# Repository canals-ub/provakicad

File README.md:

# Disseny Placa Pr&#224;ctica 5

>**Autors:** J.L. Soler, J. Canals, J.D. Prades, M. L&#243;pez

>**Versi&#243; Curs 2022/2023**

----------

## Objectiu

>PCB per practicar la soldadura de diferents tipus de components, i el test i verificaci&#243; de muntatges.

## Requisits / Especificacions

* Alimentaci&#243; 12V, regulada 5V

* Microcontrolador PIC18

* Polsadors (2x)

* Indicadors LED (2x)

* Comunicacions CAN

* Driver motor

* Sensor humitat-temperatura

* Interfície d'expansió MIKROE

## Components

| Descripci&#243; | Ref | Package |Datasheet | Prove&#239;dor | Preu | Unitats |
| --- | --- | --- | --- | ---| --- | --- |
| Microcontrolador | PIC18F26Q83-I/SS | SOIC-28 |[datasheet](https://www.mouser.es/datasheet/2/268/PIC18F27_47_57Q83_Preliminary_Data_Sheet_40002265B-2887591.pdf) | [Mouser](https://www.mouser.es/c/?q=PIC18F27Q83-I%2FSO)| 2,17&euro;| 1x |
| XTAL-Ressonador | CSTCR7M99G53-R0 | SMD |[Datasheet](https://www.mouser.es/datasheet/2/281/p16e-522700.pdf) | [Mouser](https://www.mouser.es/ProductDetail/Murata-Electronics/CSTCR7M99G53-R0?qs=Zd9RUO93%2Fo7cnwzsujIkpA%3D%3D)  | 0,27&euro; | 1x |
| CAN | MCP2551-I-SN | SOIC-8 |[Datasheet](http://ww1.microchip.com/downloads/en/devicedoc/21667d.pdf) | [Mouser](https://www.mouser.es/ProductDetail/Microchip-Technology/MCP2551T-E-SN?qs=gZwDaUDMhIcQtLtB%252B7bOWQ%3D%3D) | 1,57&euro; | 1x |
| Regulador LDO | LM317KTTR | TO-263-3| [Datasheet](https://www.ti.com/general/docs/suppproductinfo.tsp?distId=26&gotoUrl=https://www.ti.com/lit/gpn/lm317) | [Mouser](https://www.mouser.es/ProductDetail/Texas-Instruments/LM317KTTR?qs=iSMark9AYDU6ASyyp8LD6g%3D%3D) | 0,74&euro; | 1x |
| Ferrita | BLM15AX100SND | SMD 0402 | [Datasheet](https://eu.mouser.com/datasheet/2/281/ENFA0018-1915754.pdf) | [Mouser](https://eu.mouser.com/ProductDetail/Murata-Electronics/BLM15AX601SN1D?qs=MY6wChARw2zrjX4xpWbUQA%3D%3D) |  0,94&euro; | 1x |
| Sensor RH-Temp | SHT1x | | [Datasheet](https://www.sparkfun.com/datasheets/Sensors/SHT1x_datasheet.pdf) |  | | 1x |
| Rel&#233; | SR5-12V-200-1C  |- |[Datasheet](https://www.mouser.es/datasheet/2/670/sr5-2950657.pdf) | [Mouser](https://www.mouser.es/ProductDetail/CUI-Devices/SR5-12V-200-1C?qs=4ASt3YYao0WMNY1cu6cO0A%3D%3D)  | 1,17&euro; | 1x |
| Transistor | BC817-25-QR | SOT-23-3 | [Datasheet](https://www.mouser.es/datasheet/2/916/BC817_Q_SER-2498268.pdf) | [Mouser](https://www.mouser.es/ProductDetail/Nexperia/BC817-25-QR?qs=e8oIoAS2J1TYx6o1G4RDyg%3D%3D) | 0,16&euro; | 1x |
| Polsador | EVP-BT7A4A000 | SMD | [Datasheet](https://www.mouser.es/datasheet/2/315/sw_lt_eng_6s_th-2889044.pdf) | [Mouser](https://www.mouser.es/ProductDetail/Panasonic/EVP-BT7A4A000?qs=CiayqK2gdcK%2FK8JCTM%2FBCw%3D%3D) | 0,291&euro; | 3x |
| LED | 156120VS75000 green | SMD 1206 | [Datasheet](https://www.mouser.es/datasheet/2/445/156120VS75000-3085422.pdf) | [Mouser](https://www.mouser.es/ProductDetail/Wurth-Elektronik/156120VS75000?qs=2kOmHSv6VfQAUFg5BeuEfQ%3D%3D) | 0,188&euro; | 1x |
| LED | 156120RS75000 red |SMD 1206  |[Datasheet](https://www.mouser.es/datasheet/2/445/156120RS75000-3085670.pdf) | [Mouser](https://www.mouser.es/ProductDetail/Wurth-Elektronik/156120RS75000?qs=2kOmHSv6VfTlw4DhG%252BTIQw%3D%3D) | 0,188&euro; | 1x |
| Diode LDO | 1N4002T | THT axial |[Datasheet](https://www.diodes.com/assets/Datasheets/ds28002.pdf) | [Mouser](https://www.mouser.es/ProductDetail/Diodes-Incorporated/1N4002-T?qs=rGAXPo9uwV21tVJRR%252BhxrQ%3D%3D) | 0,169&euro; | 3x |
| Diode transil | SMAJ15A-TR | SMD/SMT|[Datasheet](https://www.mouser.es/datasheet/2/389/smaj10ca-2956135.pdf) | [Mouser](https://www.mouser.es/ProductDetail/STMicroelectronics/SMAJ15A-TR?qs=fMNaVbI0QcP5ezTdgkCxZA%3D%3D) | 0,404&euro; | 1x |
| Capacitat 100nF | C0805C104M5RACTU | SMD 0805 |[Datasheet](https://www.mouser.es/datasheet/2/212/KEM_C1002_X7R_SMD-1102033.pdf) | [Mouser](https://www.mouser.es/ProductDetail/KEMET/C0805C104M5RACTU?qs=VOOUd%252Bza08qHu13WgNByHQ%3D%3D) | 0,022&euro; | 6x |
| Capacitat 10uF | MCASE32NSB5106MTNA01 | SMD 1210 |[Datasheet](https://www.mouser.es/datasheet/2/396/Taiyo_Yuden_1102023_MC_mlcc_all_e-3081584.pdf) | [Mouser](https://www.mouser.es/ProductDetail/TAIYO-YUDEN/MCASE32NSB5106MTNA01?qs=sGAEpiMZZMuMW9TJLBQkXugdD5SwFUVx3SlCD21BkBE%3D) | 0,30&euro; | 1x |
| Capacitat 1uF | 860020672005 | THT Radial 5mm |[Datasheet](https://www.mouser.es/datasheet/2/445/860020672005-3099424.pdf) | [Mouser](https://www.mouser.es/ProductDetail/TAIYO-YUDEN/MCASE32NSB5106MTNA01?qs=sGAEpiMZZMuMW9TJLBQkXugdD5SwFUVx3SlCD21BkBE%3D) | 0,084&euro; | 1x |
| Connectors | 10129378-910002BLF| tira pins poste 2.54 |[Datasheet](https://cdn.amphenol-cs.com/media/wysiwyg/files/documentation/datasheet/boardwiretoboard/bwb_econostik_254headers.pdf) | [Mouser](https://www.mouser.es/ProductDetail/Amphenol-FCI/10129378-910002BLF?qs=0lQeLiL1qyYh8zFHsKDebQ%3D%3D) |0,18&euro; | x19 |
| Resist&#232;ncies | diverses | SMD 1206 | |  | | 11x |

## Historial de canvis

| Data | Autor     | Branch | Versi&#243; | Descripci&#243; |
| --- | --- | --- | --- | --- |
|  28/03/2023 | mlopez | Master | initial commit | Primera versi&#243; d'esquem&#224;tic i selecci&#243; de components |
|  30/03/2023 | dprades | P5 | v1 | Reselecci&#243; de components disponibles a mercat |
|  04/04/2023 | dprades | P5 | v2 | Esquem&#224;tic final i placement |
|  05/04/2023 | jcanals | P5 | v3 | Candidata a producci&#243; |
|  06/04/2023 | jcanals | P5 | v4 | Arreglat el Vadj del regulador.  |
|  20/04/2023 | dprades | P5 | v5 | Arreglats footprints uC, transil, switch i ferrita. |
|  20/04/2023 | dprades | P5 | v5.1 | Correccions menors format. |

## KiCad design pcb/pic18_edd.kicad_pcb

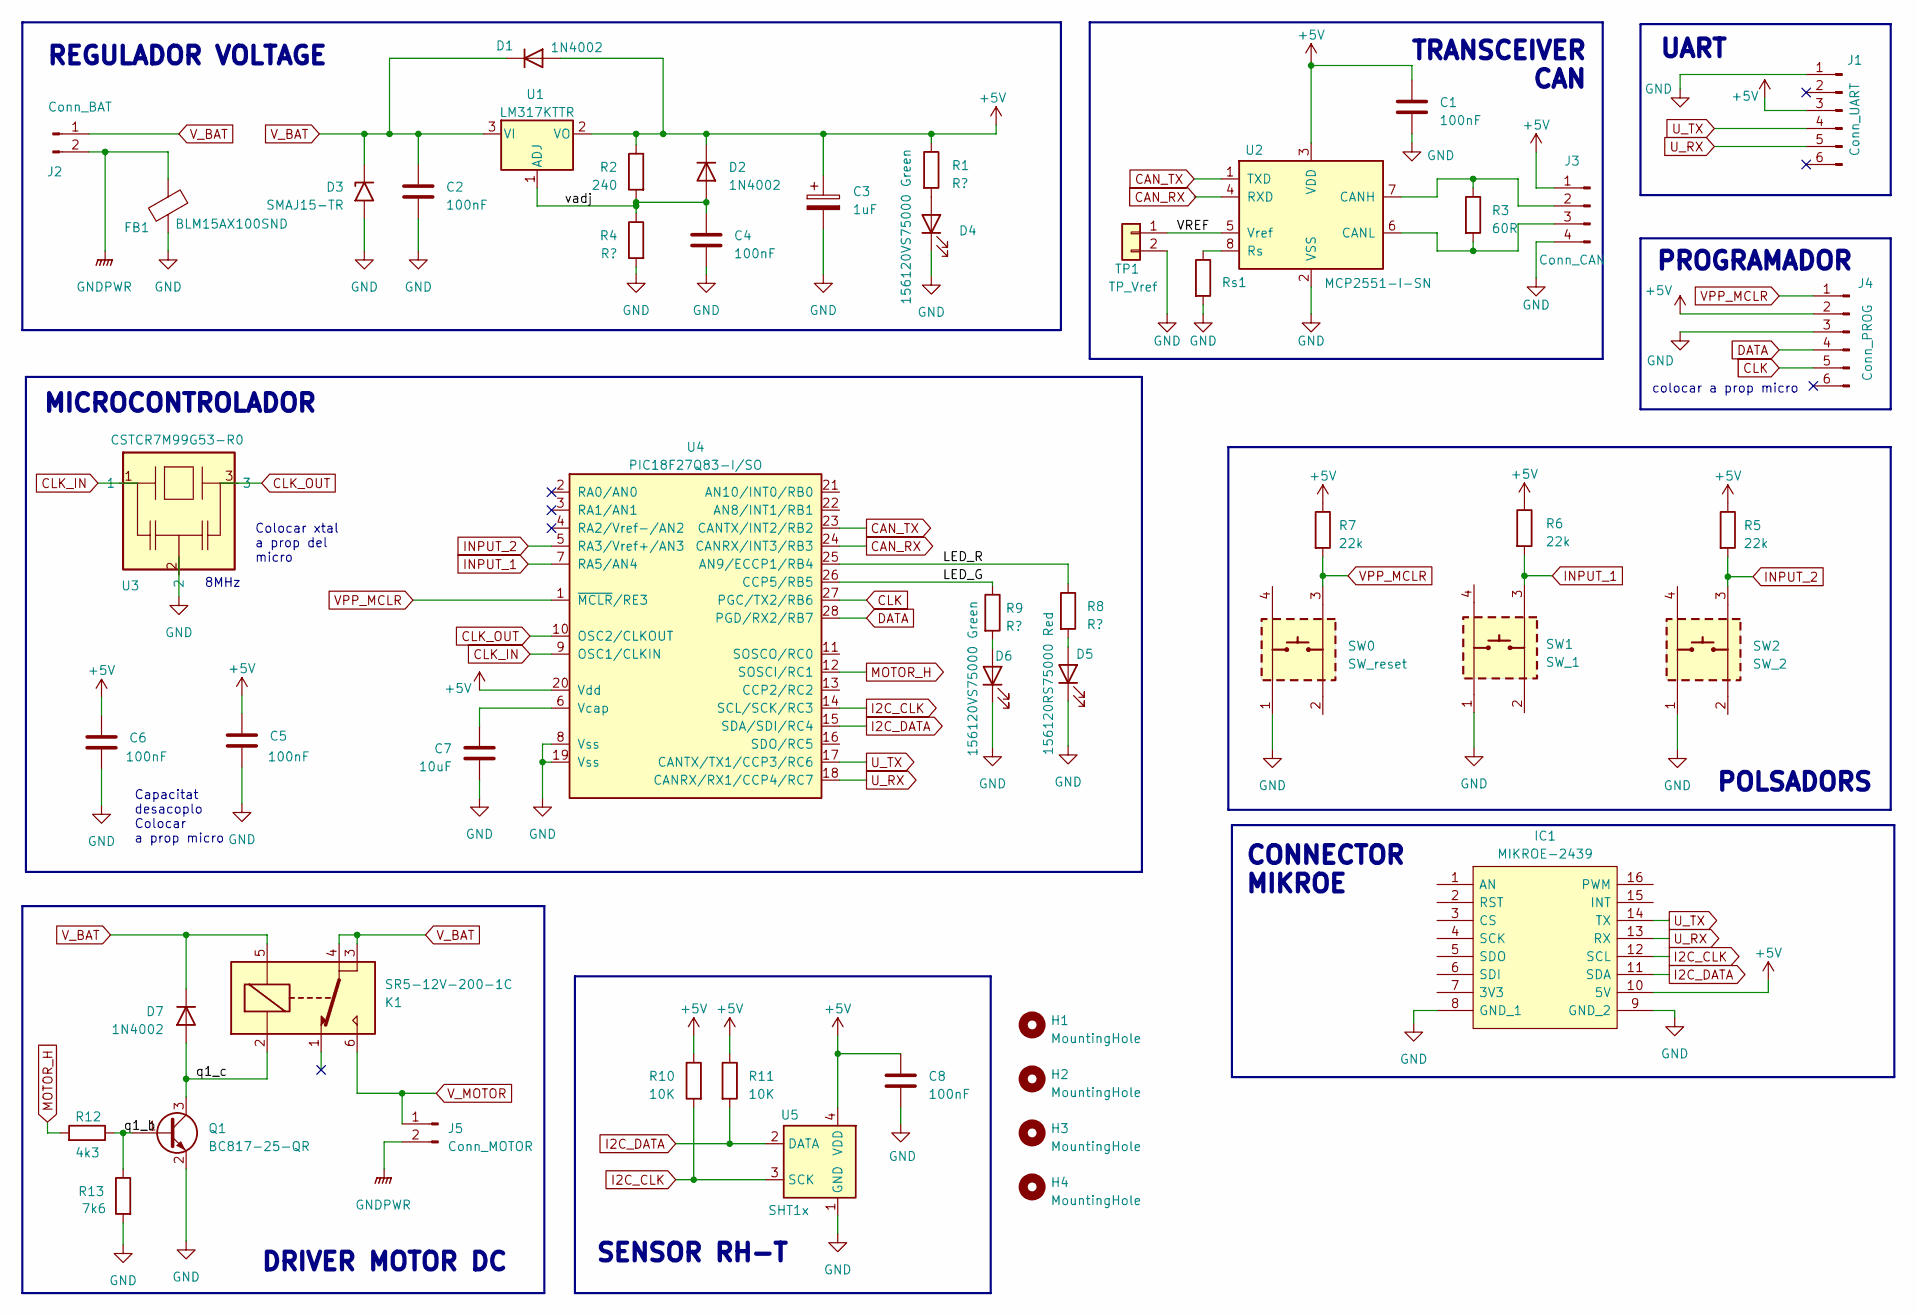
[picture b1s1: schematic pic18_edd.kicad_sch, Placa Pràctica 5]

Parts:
C1, C2, C4, C5, C6, C8: 100nF; C_1206_3216Metric
C3: 1uF; CP_Radial_D5.0mm_P2.00mm
C7: 10uF; C_1210_3225Metric_Pad1.33x2.70mm_HandSolder
D1, D2, D7: 1N4002; D_DO-41_SOD81_P10.16mm_Horizontal
D3: SMAJ15-TR; D_SMA_Handsoldering
D4, D6: 156120VS75000 Green; LED_1206_3216Metric_Pad1.42x1.75mm_HandSolder
D5: 156120RS75000 Red; LED_1206_3216Metric_Pad1.42x1.75mm_HandSolder
FB1: BLM15AX100SND; L_0402_1005Metric_Pad0.77x0.64mm_HandSolder
H1, H2, H3, H4: MountingHole; MountingHole_3.2mm_M3
IC1: MIKROE-2439; mikroe_s; Manufacturer_Part_Number MIKROE-2439; Mouser Part Number 932-MIKROE-2439
J1: Conn_UART; PinSocket_1x06_P2.54mm_Vertical
J2: Conn_BAT; PinSocket_1x02_P2.54mm_Vertical
J3: Conn_CAN; PinSocket_1x04_P2.54mm_Vertical
J4: Conn_PROG; PinSocket_1x06_P2.54mm_Vertical
J5: Conn_MOTOR; PinSocket_1x02_P2.54mm_Vertical
K1: SR5-12V-200-1C; DIP-6_300_ELL
Q1: BC817-25-QR; SOT-23
R1, R4, R8, R9: R?; R_1206_3216Metric_Pad1.30x1.75mm_HandSolder
R2: 240; R_1206_3216Metric_Pad1.30x1.75mm_HandSolder
R3: 60R; R_1206_3216Metric_Pad1.30x1.75mm_HandSolder
R5, R6, R7: 22k; R_1206_3216Metric_Pad1.30x1.75mm_HandSolder
R10, R11: 10K; R_1206_3216Metric_Pad1.30x1.75mm_HandSolder
R12: 4k3; R_1206_3216Metric_Pad1.30x1.75mm_HandSolder
R13: 7k6; R_1206_3216Metric_Pad1.30x1.75mm_HandSolder
Rs1: R_1206_3216Metric_Pad1.30x1.75mm_HandSolder
SW0: SW_reset; Push_btn_SMD_sqr_handsoldering
SW1: SW_1; Push_btn_SMD_sqr_handsoldering
SW2: SW_2; Push_btn_SMD_sqr_handsoldering
TP1: TP_Vref; PinSocket_1x02_P2.54mm_Vertical
U1: LM317KTTR; TO-263-3_TabPin2
U2: MCP2551-I-SN; SOIC-8_3.9x4.9mm_P1.27mm
U3: CSTCR7M99G53-R0; SMD_XTAL
U4: PIC18F27Q83-I/SO; SOIC-28W_7.5x18.7mm_P1.27mm
U5: SHT1x

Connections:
+5V: C1.1, C3.1, C5.1, C6.1, C8.1, D1.2 (A), D2.1 (K), IC1.10 (5V), J1.3, J3.1, J4.2, R1.1, R2.1, R5.1, R6.1, R7.1, R10.1, R11.1, U1.2 (VO), U2.3 (VDD), U4.20 (Vdd), U5.4 (VDD)
/LED_G: R9.1, U4.26 (CCP5/RB5)
/LED_R: R8.1, U4.25 (AN9/ECCP1/RB4)
/VREF: TP1.1, U2.5 (Vref)
/q1_b: Q1.1 (B), R12.1, R13.1
/q1_c: D7.2 (A), K1.2, Q1.3 (C)
/vadj: C4.1, D2.2 (A), R2.2, R4.1, U1.1 (ADJ)
CAN_RX: U2.4 (RXD), U4.24 (CANRX/INT3/RB3)
CAN_TX: U2.1 (TXD), U4.23 (CANTX/INT2/RB2)
CLK: J4.5, U4.27 (PGC/TX2/RB6)
CLK_IN: U3.1, U4.9 (OSC1/CLKIN)
CLK_OUT: U3.3, U4.10 (OSC2/CLKOUT)
DATA: J4.4, U4.28 (PGD/RX2/RB7)
GND: C1.2, C2.2, C3.2, C4.2, C5.2, C6.2, C7.2, C8.2, D3.2 (A2), D4.1 (K), D5.1 (K), D6.1 (K), FB1.2, IC1.8 (GND_1), IC1.9 (GND_2), J1.1, J3.4, J4.3, Q1.2 (E), R4.2, R13.2, Rs1.2, SW0.1, SW1.1, SW2.1, TP1.2, U2.2 (VSS), U3.2, U4.8 (Vss), U4.19 (Vss), U5.1 (GND)
GNDPWR: FB1.1, J2.2, J5.2
I2C_CLK: IC1.12 (SCL), R10.2, U4.14 (SCL/SCK/RC3), U5.3 (SCK)
I2C_DATA: IC1.11 (SDA), R11.2, U4.15 (SDA/SDI/RC4), U5.2 (DATA)
INPUT_1: R6.2, SW1.3, U4.7 (RA5/AN4)
INPUT_2: R5.2, SW2.3, U4.5 (RA3/Vref+/AN3)
MOTOR_H: R12.2, U4.12 (SOSCI/RC1)
unnamed: D4.2 (A), R1.2
unnamed: D5.2 (A), R8.2
unnamed: D6.2 (A), R9.2
unnamed: J3.2, R3.1, U2.7 (CANH)
unnamed: J3.3, R3.2, U2.6 (CANL)
unnamed: Rs1.1, U2.8 (Rs)
unnamed: C7.1, U4.6 (Vcap)
U_RX: IC1.13 (RX), J1.5, U4.18 (CANRX/RX1/CCP4/RC7)
U_TX: IC1.14 (TX), J1.4, U4.17 (CANTX/TX1/CCP3/RC6)
VPP_MCLR: J4.1, R7.2, SW0.3, U4.1 (~MCLR/RE3)
V_BAT: C2.1, D1.1 (K), D3.1 (A1), D7.1 (K), J2.1, K1.3, K1.4, K1.5, U1.3 (VI)
V_MOTOR: J5.1, K1.6

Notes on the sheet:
PROGRAMADOR
Colocar xtal a prop del micro
DRIVER MOTOR DC
CONNECTOR MIKROE
TRANSCEIVER CAN
8MHz
REGULADOR VOLTAGE
MICROCONTROLADOR
SENSOR RH-T
UART
colocar a prop micro
POLSADORS
Capacitat desacoplo Colocar a prop micro

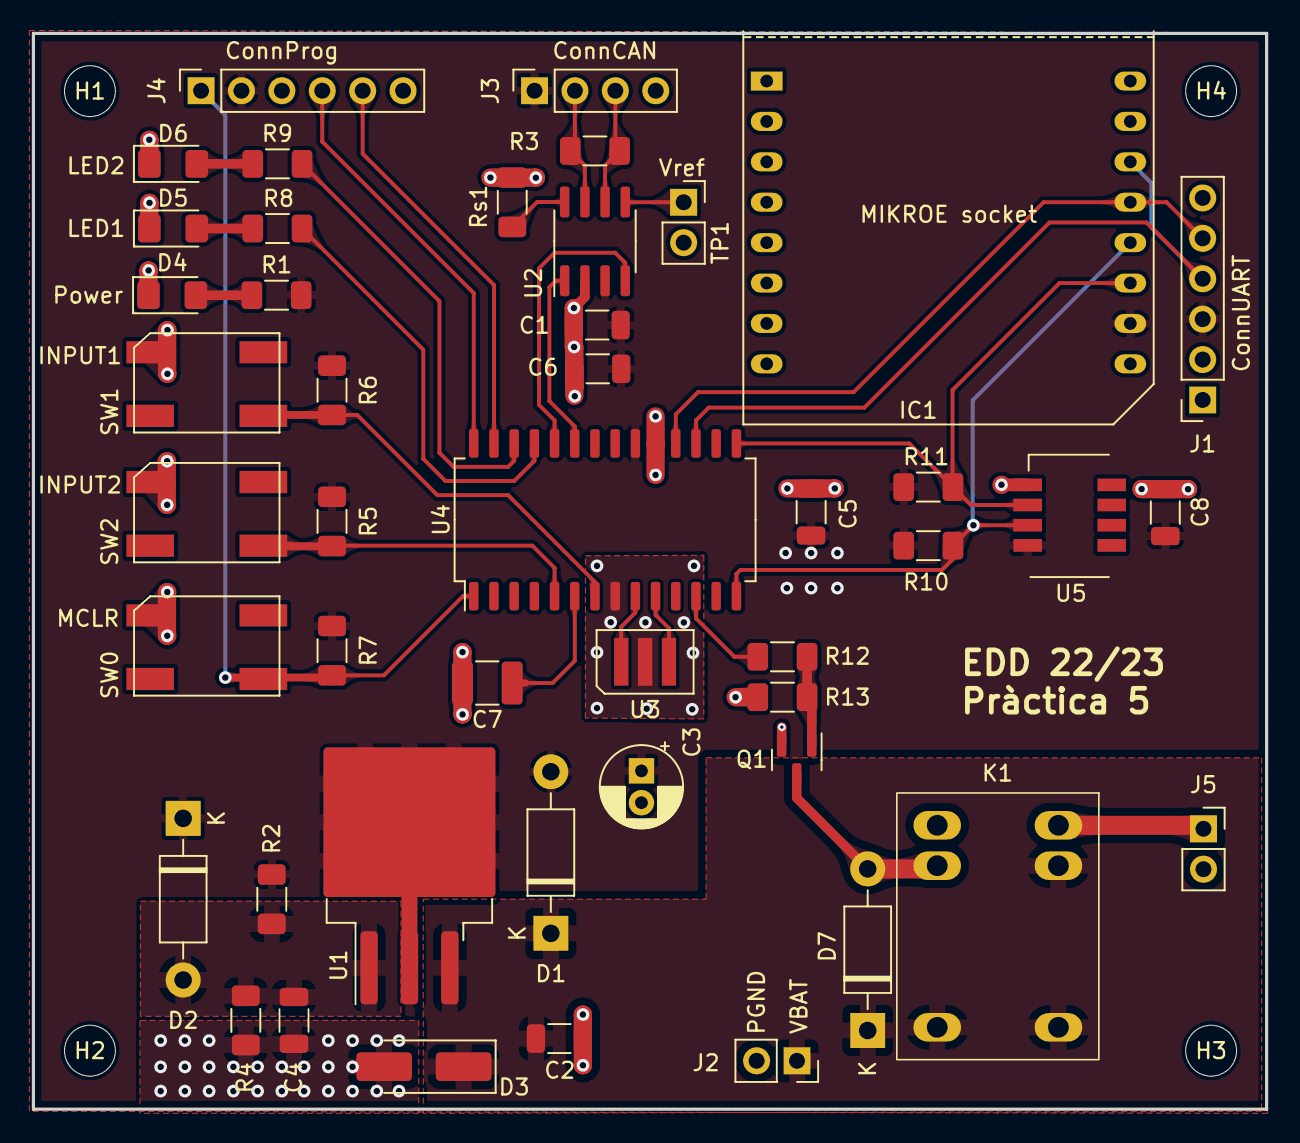
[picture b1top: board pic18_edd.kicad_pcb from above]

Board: 2 copper layers, 77.5 x 67.6 mm, 51 parts (1 on the bottom side), 32 nets.

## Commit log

2023-04-21 all in
2023-04-21 not all
2023-04-21 pcb folder
2023-05-04 last version
